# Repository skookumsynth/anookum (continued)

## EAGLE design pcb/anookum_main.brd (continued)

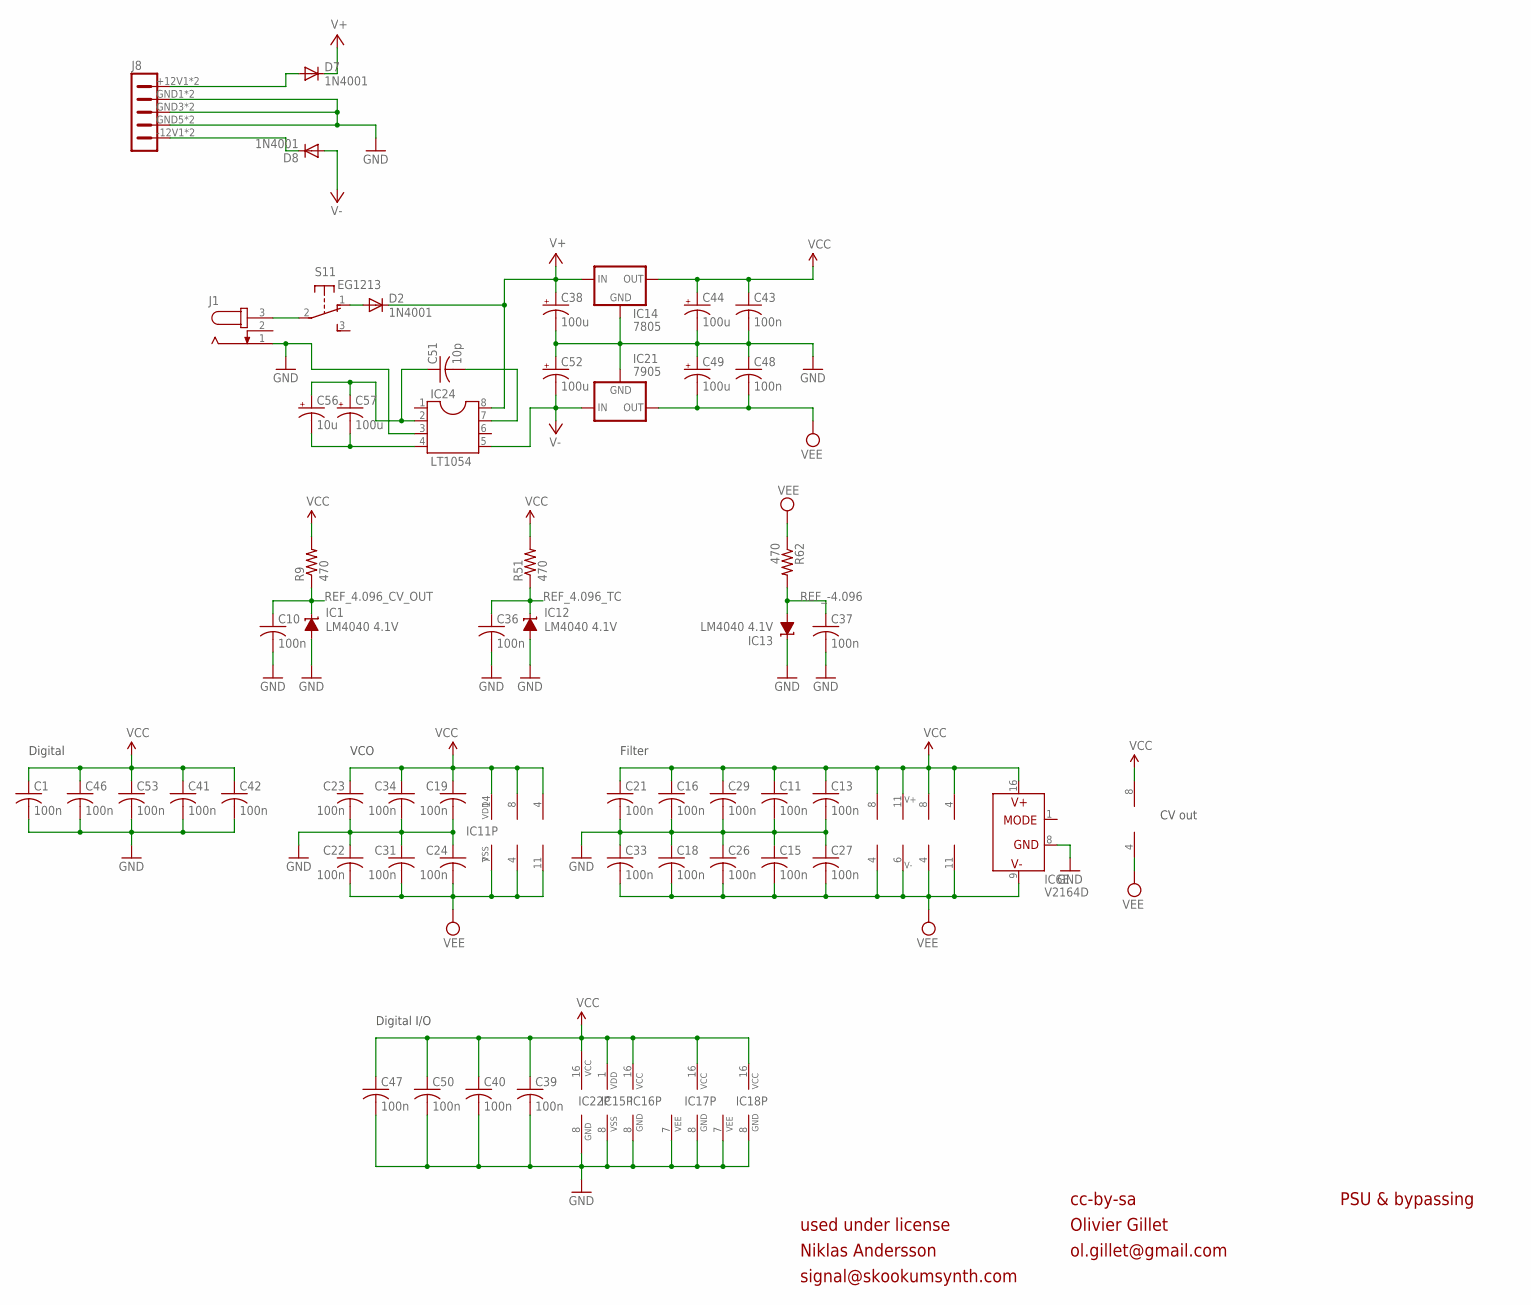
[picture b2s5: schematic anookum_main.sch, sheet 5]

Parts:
C1, C10, C11, C13, C15, C16, C18, C19, C21, C22, C23, C24, C26, C27, C29, C31, C33, C34, C36, C37, C39, C40, C41, C42, C43, C46, C47, C48, C50, C53: 100n; C025-025X050
C38, C44, C49, C52: 100u; E2,5-7
C51: 10p; C025-025X050
C56: 10u; E2,5-5
C57: 100u; E2,5-6
D2, D7, D8: 1N4001; DO41-10
IC1, IC12, IC13: LM4040 4.1V; LP_O-PBCY-W3
IC2: TS912; DIL08
IC3, IC7, IC9: TL072P; DIL08
IC4: LM13700N; DIL16
IC5, IC10: TL074; DIL14
IC6: V2164D; DIL16
IC11: 4024N; DIL14
IC14: 7805; 78XXS
IC15: 4050N; DIL16
IC16: 74HC595N; DIL16
IC17, IC18: 4051N; DIL16
IC21: 7905; 79XXS
IC22: 74HC165N; DIL16
IC24: LT1054; DIL08
J1: JACK-PLUG2; SPC4078_BIG_HOLES
J8: HDR_POWER_10_VERT; HDR_POWER_10
R9, R51, R62: 470; 0204/7
S1: EG1213

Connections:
GND: C1.2, C10.2, C11.2, C13.2, C15.1, C16.2, C18.1, C19.2, C21.2, C22.1, C23.2, C24.1, C26.1, C27.1, C29.2, C31.1, C33.1, C34.2, C36.2, C37.2, C38.-, C39.2, C40.2, C41.2, C42.2, C43.2, C44.-, C46.2, C47.2, C48.1, C49.+, C50.2, C52.+, C53.2, IC1.3 (A), IC6.8 (GND), IC12.3 (A), IC13.2 (C), IC14.GND, IC15.8 (VSS), IC16.8 (GND), IC17.7 (VEE), IC17.8 (GND), IC18.7 (VEE), IC18.8 (GND), IC21.GND, IC22.8 (GND), IC24.3, J1.1, J8.GND1 (2), J8.GND2 (2), J8.GND3 (3), J8.GND4 (3), J8.GND5 (4), J8.GND6 (4); also elsewhere on the board
unnamed: J1.3, S1.2
unnamed: D2.A, S1.1 (O)
unnamed: C51.1, C56.+, C57.+, IC24.2
unnamed: D7.A, J8.+12V1 (1), J8.+12V2 (1)
unnamed: D8.C, J8.-12V1 (5), J8.-12V2 (5)
unnamed: C56.-, C57.-, IC24.4
unnamed: C51.2, IC24.7
REF_4.096_CV_OUT: C10.1, IC1.2 (C), R9.1; also elsewhere on the board
REF_4.096_TC: C36.1, IC12.2 (C), R51.1; also elsewhere on the board
REF_-4.096: C37.1, IC13.3 (A), R62.2; also elsewhere on the board
V+: C38.+, D2.C, D7.C, IC14.IN, IC24.8
V-: C52.-, D8.A, IC21.IN, IC24.5
VCC: C1.1, C11.1, C13.1, C16.1, C19.1, C21.1, C23.1, C29.1, C34.1, C39.1, C40.1, C41.1, C42.1, C43.1, C44.+, C46.1, C47.1, C50.1, C53.1, IC2.8 (V+), IC3.8 (V+), IC4.11 (V+), IC5.4 (V+), IC6.16 (V+), IC7.8 (V+), IC9.8 (V+), IC10.4 (V+), IC11.14 (VDD), IC14.OUT, IC15.1 (VDD), IC16.16 (VCC), IC17.16 (VCC), IC18.16 (VCC), IC22.16 (VCC), R9.2, R51.2; also elsewhere on the board
VEE: C15.2, C18.2, C22.2, C24.2, C26.2, C27.2, C31.2, C33.2, C48.2, C49.-, IC2.4 (V-), IC3.4 (V-), IC4.6 (V-), IC5.11 (V-), IC6.9 (V-), IC7.4 (V-), IC9.4 (V-), IC10.11 (V-), IC11.7 (VSS), IC21.OUT, R62.1; also elsewhere on the board

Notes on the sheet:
Digital
VCO
Filter
CV out
cc-by-sa
Olivier Gillet
ol.gillet@gmail.com
PSU & bypassing
Digital I/O
used under license
Niklas Andersson
signal@skookumsynth.com

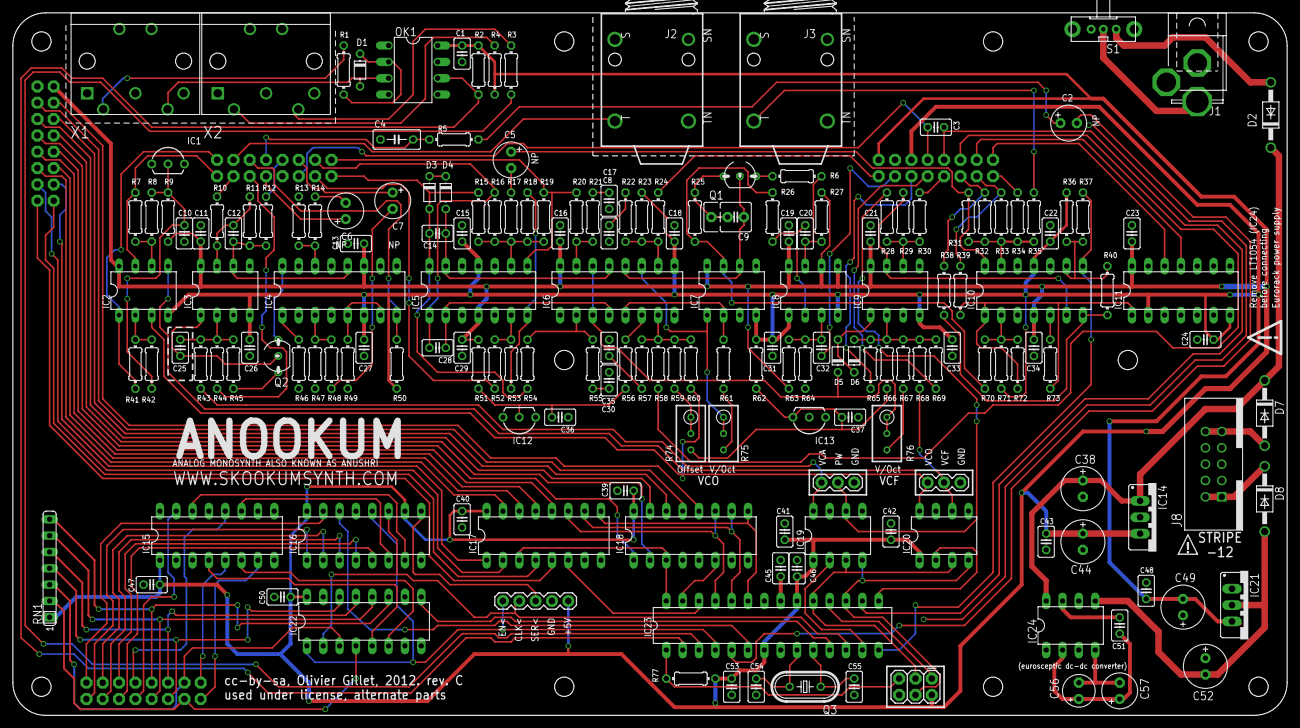
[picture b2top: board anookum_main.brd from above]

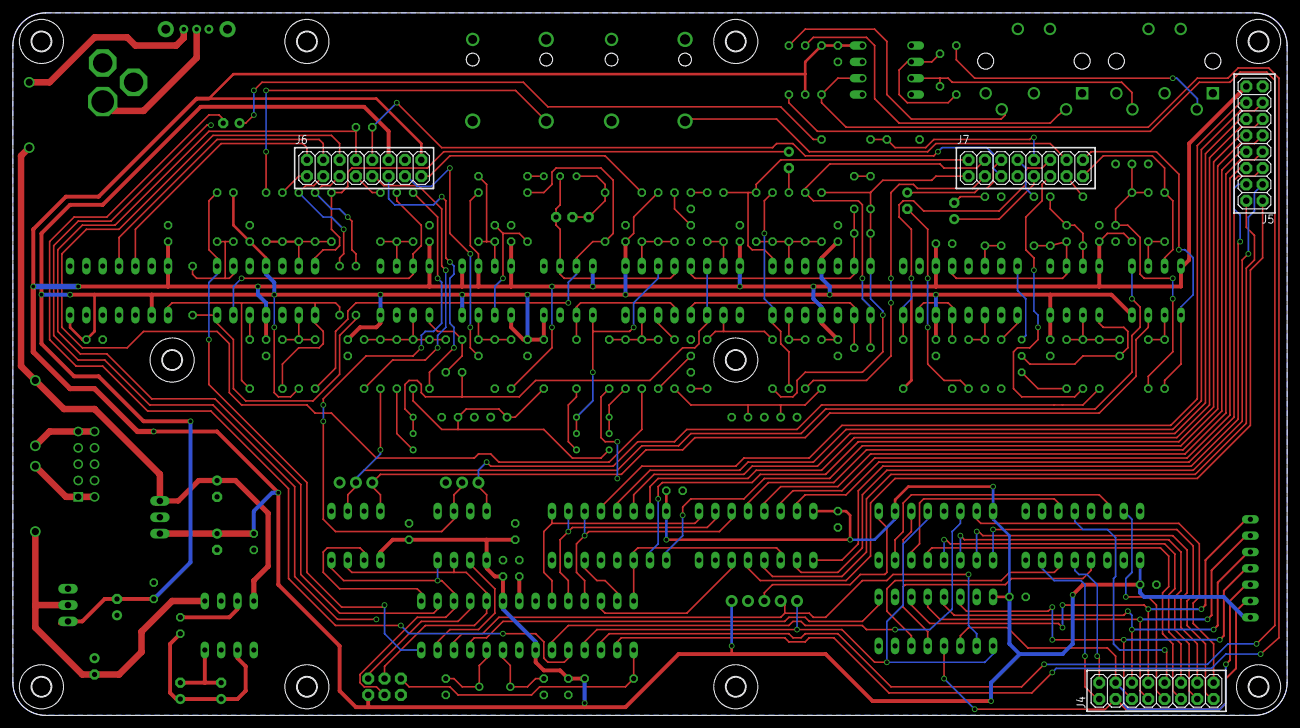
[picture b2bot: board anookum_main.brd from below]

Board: 2 copper layers, 198.1 x 109.2 mm, 196 parts (14 on the bottom side), 165 nets.

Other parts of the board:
U$3, U$4, U$5, U$6, U$7, U$8, U$9, U$10, U$11, U$12: 3,0

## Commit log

2016-05-30 :boom::camel: Added .gitattributes
2016-05-30 tidying
2016-06-01 cleaning
2016-06-04 new bom
2016-06-09 Revised
    10kA ->100kA
